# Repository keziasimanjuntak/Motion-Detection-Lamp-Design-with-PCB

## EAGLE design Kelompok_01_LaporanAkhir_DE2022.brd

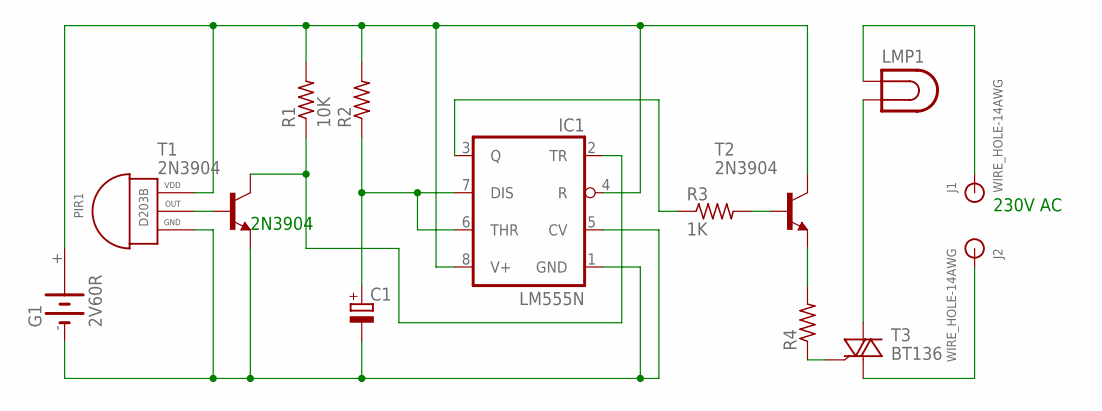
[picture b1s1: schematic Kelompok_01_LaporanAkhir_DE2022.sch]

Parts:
C1: CPOL-EUB45181C; B45181C
G1: 2V60R
IC1: LM555N; DIL08
J1, J2: WIRE_HOLE-14AWG
LMP1: LAMP; LDH-5R
PIR1: D203B; 3PIN
R1: 10K; 0204/7
R2, R4: R-US_0204/7; 0204/7
R3: 1K; 0204/7
T1, T2: 2N3904; TO92
T3: BT136; TO220AB

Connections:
unnamed: PIR1.2 (OUT), T1.2 (B)
unnamed: IC1.2 (TR), R1.1, T1.1 (C)
unnamed: G1.+, IC1.4 (R), IC1.8 (V+), PIR1.1 (VDD), R1.2, R2.2, T2.1 (C)
unnamed: C1.-, G1.-, IC1.1 (GND), IC1.5 (CV), PIR1.3 (GND), T1.3 (E)
unnamed: C1.+, IC1.6 (THR), IC1.7 (DIS), R2.1
unnamed: IC1.3 (Q), R3.1
unnamed: R3.2, T2.2 (B)
unnamed: R4.2, T2.3 (E)
unnamed: R4.1, T3.3 (G)
unnamed: LMP1.2, T3.2 (A2)
unnamed: J1.P$1, LMP1.1
unnamed: J2.P$1, T3.1 (A1)

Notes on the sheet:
2N3904
230V AC

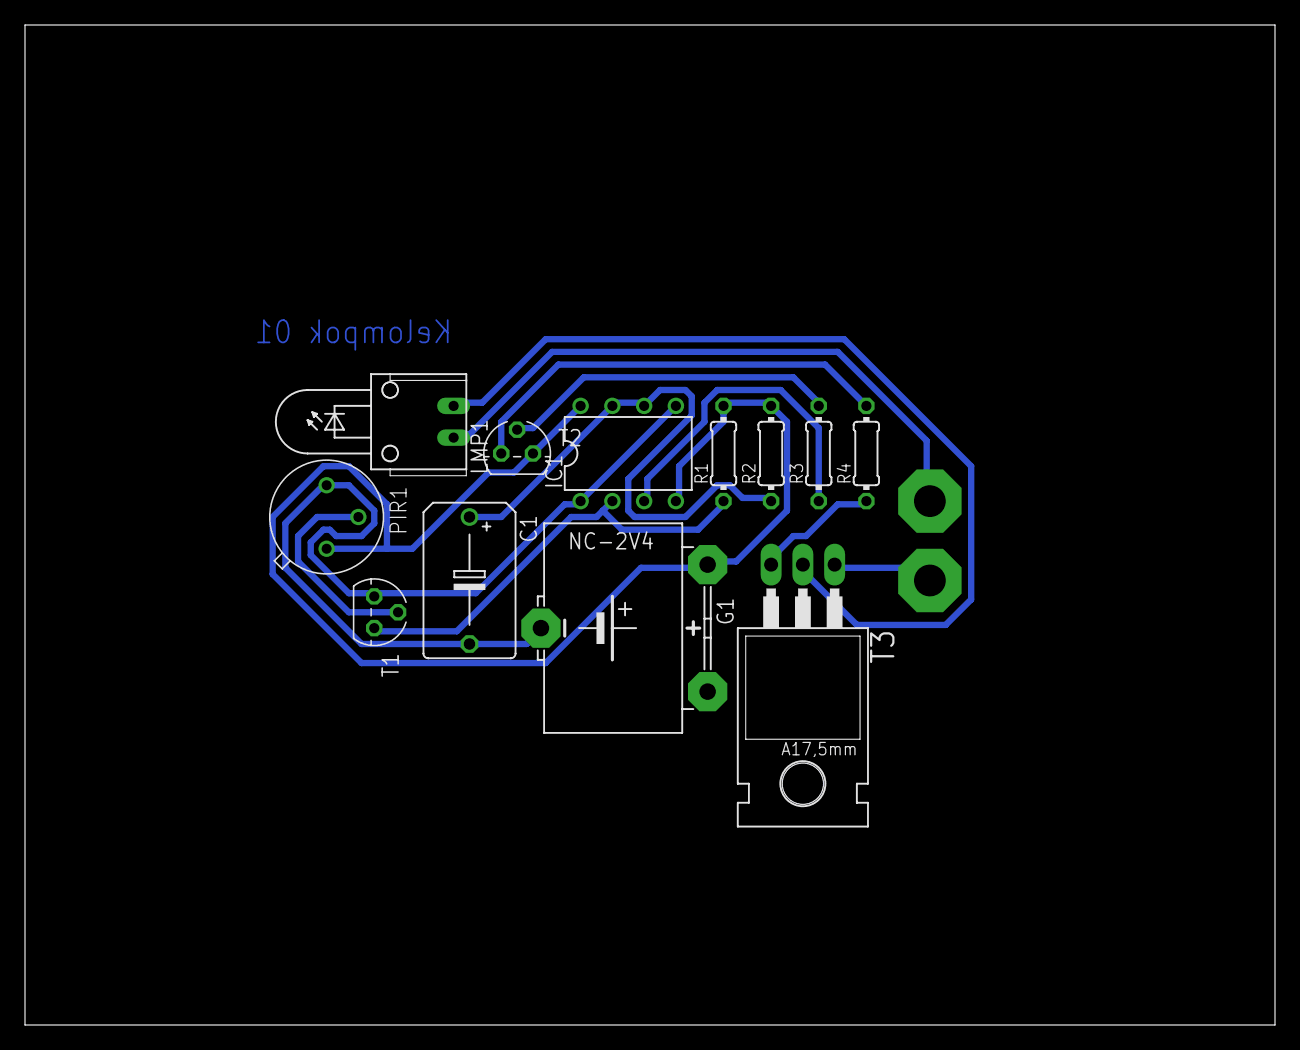
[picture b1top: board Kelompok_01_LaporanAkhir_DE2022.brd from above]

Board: 2 copper layers, 100.0 x 80.0 mm, 14 parts (0 on the bottom side), 12 nets.
